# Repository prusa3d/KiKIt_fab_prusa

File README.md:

# Prusaman: Automatické generování výrobních podkladů z KiCADu

Prusaman je samostatní command-linový nástroj a doplněk do KiCADu, který
umožňuje automaticky generovat veškeré výrobní podklady pro PCB (panelizace,
Gerbery pro výrobce, data pro frézku, data pro osazovačku a lepidlo a nákupní
seznam). Celý proces je řízen jedním konfiguračním souborem `prusaman.yaml`
umístěným v kořenovém adresáři projektu.

Co by tě mohlo zajímat?

- [Instalace a aktualizace](doc/installation.md)
- [Konfigurace projektu](doc/configuration.md)
- [Používání nástroje](doc/usage.md)
- Pokud něco nefunguje, je třeba otevřit [issue na
  GitHubu](https://github.com/prusa3d/KiKIt_fab_prusa/issues).

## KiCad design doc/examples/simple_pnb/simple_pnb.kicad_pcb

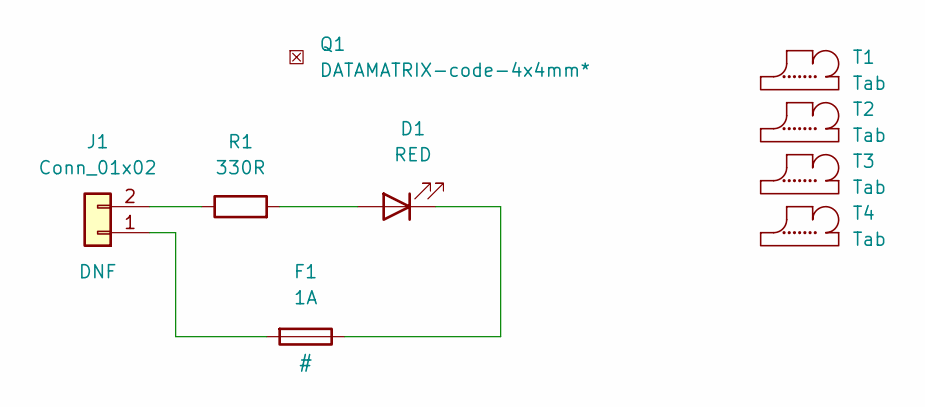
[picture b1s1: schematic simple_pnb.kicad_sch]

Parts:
D1: RED; LED_0603_1608Metric
F1: 1A; Fuse_Blade_ATO_directSolder
J1: Conn_01x02; PinHeader_1x02_P2.54mm_Horizontal
Q1: G_DATAMATRIX-code-4x4mm*; Datamatyrix-code-4x4mm; part_value DATAMATRIX-code-4x4mm*
R1: 330R; R_0603_1608Metric
T1, T2, T3, T4: Tab; Tab_2mm

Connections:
unnamed: D1.1 (K), F1.1
unnamed: D1.2 (A), R1.2
unnamed: F1.2, J1.1
unnamed: J1.2, R1.1

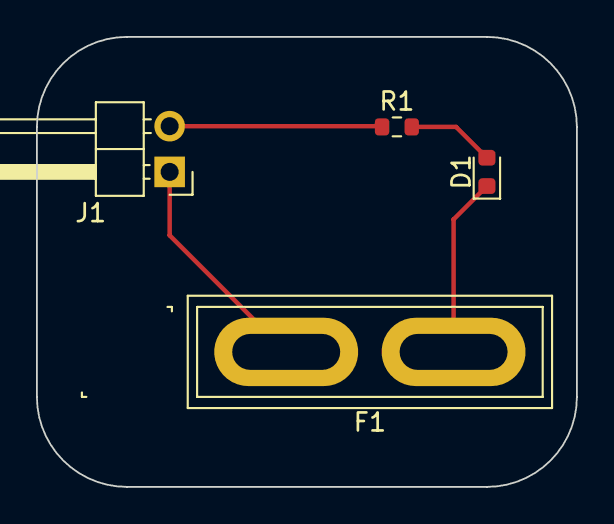
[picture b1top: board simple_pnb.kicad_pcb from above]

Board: 2 copper layers, 30.0 x 25.0 mm, 9 parts (0 on the bottom side), 4 nets.

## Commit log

2022-04-04 Draft panel and freza stages
2022-04-12 Implement all functionality for making a project
2022-04-13 Add GUI plugin
2022-04-13 Add CI
2022-04-13 Add documentation
2022-04-13 Clarify glue
2022-04-14 Fix typo in variable name
2022-04-22 Add missing subpackages
2022-04-22 Improve Windows compatibility
2022-04-24 Report errors properly
2022-04-25 Get rid of Prusalib depndency as submodule
2022-04-25 Generate nicer errors on unknown variables in text
2022-04-25 Make errors about missing templates more user friendly
2022-04-25 Report errors clearly in GUI
2022-04-27 Improve UI responsivness
2022-04-27 Implement custom error dialog to show stacktraces
2022-04-27 Improve UI
2022-04-27 Do not yield version warning in iBom
2022-05-02 Make it work on Debian
2022-05-02 Include Prusaman version in CI
2022-05-04 Implement PnB BOM filter
2022-05-04 Implement DMC text
2022-05-10 Preserve iBom version correctly
2022-05-10 Make CI artifact directly usable
2022-05-10 Add basic tests to CI
2022-05-10 Bake iBom version
2022-05-10 Fix double newline on Windows in CSV files.
2022-05-11 Support Flatpak KiCAD
2022-05-11 Assume that ensurepip might fail
2022-05-11 Allow cross-device locations
2022-05-11 Implement new style sourcing BOM
2022-05-11 Update documentation doc
2022-05-11 Update installation instructions
2022-05-13 Show Prusaman version
2022-05-13 Pack KiKit with Prusaman
2022-05-13 Use KiKit plugins for Prusa specific tasks
2022-05-15 Use upstream version of KiKit in CI
2022-05-15 Fix installation on Windows with path containing whitespace
2022-05-15 Implement text variables
2022-05-16 Warn user if the schematics is not annotated
2022-05-16 Make the process more verbose
2022-05-16 Show ID and use dark mode in iBom
2022-05-16 Update example with backbone
2022-05-17 Update the example with copperfill
2022-05-17 Update the example so custom tab symbols are used
2022-05-17 Drop KiCAD v5 support
2022-05-17 Supply extra fields to iBom via netlist
2022-05-18 Fix output directory and ask the user if they want to open it
2022-05-18 Include PnB in iBom
2022-05-18 Translate PnB fields
2022-05-18 Remove prusaman.yaml
2022-05-18 Generate panel ibom for only a single board
2022-05-18 Change naming and content of ZIP files
2022-05-18 Add ID to POS files
2022-05-18 Use only newstyle BOM for sourcing
2022-05-19 Reorder columns
2022-05-19 Properly read comments in schematic titlesheet
2022-05-19 Yield better error message in the text plugin
2022-05-19 Decouple Kikit from Prusaman
2022-05-19 Update installation
2022-05-19 Use local temp directories
2022-05-19 Tweak SMT stage
2022-05-19 Yield better KiKit errors
2022-05-23 Change hard-coded constant in framing
2022-05-23 Disable aparture macro in gerbers
2022-05-23 Make Fiducials magical
2022-05-23 Make milled slot the same width as board spacing
2022-05-23 Implement 3D model synchronization
2022-05-24 Fix GUI import
2022-05-24 Add final archive
2022-05-25 Implement design rules
2022-05-25 Run DRC for the board and the panel
2022-05-25 Add stackup variable
2022-05-25 Implement other text variables
2022-05-25 Add color output in GUI
2022-05-25 Do not break stackup
2022-05-26 Update default parameters
2022-05-26 Treat DRC warnings are warnings
2022-05-26 Implement the basics of footprint check
2022-06-06 Add source files into the production data
2022-06-06 Restructure manugenerator and distinguish between bugs and user errors
2022-06-06 Run iBOM in headless mode
2022-06-07 Add excessive logging for the log file
2022-06-08 Prevent recursive archives when using source directory as the output directory
2022-06-08 Fix error formatting
2022-06-20 Show board thickness in stackup variable
2022-06-20 Escape comma in pos file
2022-06-20 Prevent infinite loop when packing source data
2022-06-20 Do not subtract mask from silkscreen
2022-06-20 Make ibom verbose
2022-06-20 Update hole4cutter
2022-06-22 Implement footprint revision check
2022-06-28 new rules
2022-06-28 Speed up footprint version check
2022-06-28 Use PnB for all symbols
2022-06-28 Change wording in iBom
2022-06-30 add rule clearance 0.11 trackwidth 0.15 minthroughhole 0.3
2022-07-04 Fix bug with not all source files being copied
2022-07-07 add rule clearance0.1_track0.1_hole0.2_0.4viadim
